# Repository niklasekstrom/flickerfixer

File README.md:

# flickerfixer
An open source flicker fixer for Amiga 500/2000

This is the first stage in the construction of a flicker fixer/scan doubler that mounts internally in an Amiga 500 or Amiga 2000.

In order to rapidly prototype the FPGA logic I designed a small adapter board that connects pins on Denise to a [DE10-Lite](http://de10-lite.terasic.com/) FPGA development board via a 5V-tolerant buffer. The KiCad files for the board are available in [Hardware](Hardware).

After ordering, receiving and soldering the PCB I then wrote Verilog code that samples CSYNC (composite sync) and the 12-bit RGB signals, and outputs the sampled pixels to VGA. The logic handles both non-interlaced and interlaced output from the Amiga. The Quartus project is available in [HDL](HDL).

The next stage is to design a stand-alone board that contains an [FPGA](https://www.mouser.se/ProductDetail/Intel-Altera/10M02SCE144C8G?qs=G%2FX6g08h60tD7HZOc4xZbg%3D%3D) chip and an [SDRAM](https://www.mouser.se/ProductDetail/ISSI/IS42S16400J-6TL?qs=sGAEpiMZZMti5BT4iPSEnRbV70NKySN8V%252BBluA5se8I%3D) chip.

Some pictures:

|         |            |
| ------------- |---------------|
|  |  |
| |  |

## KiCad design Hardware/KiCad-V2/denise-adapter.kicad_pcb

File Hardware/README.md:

# Components

* A single [74LCX16244](https://www.mouser.se/ProductDetail/ON-Semiconductor-Fairchild/74LCX16244MTD?qs=sGAEpiMZZMuiiWkaIwCK2a5G6tOfghZ%2FVIxKNPvFHco%3D) buffer chip is used to translate 5V to 3.3V.
* Four 100 nF decoupling capacitors, 1206 size, are mounted on the back of the PCB.
* A 48 pin DIP socket.
* A 48 pin DIP socket whose pins going both up and down, and the legs going down are thinner.
* A 2x20 pin ribbon cable connector.

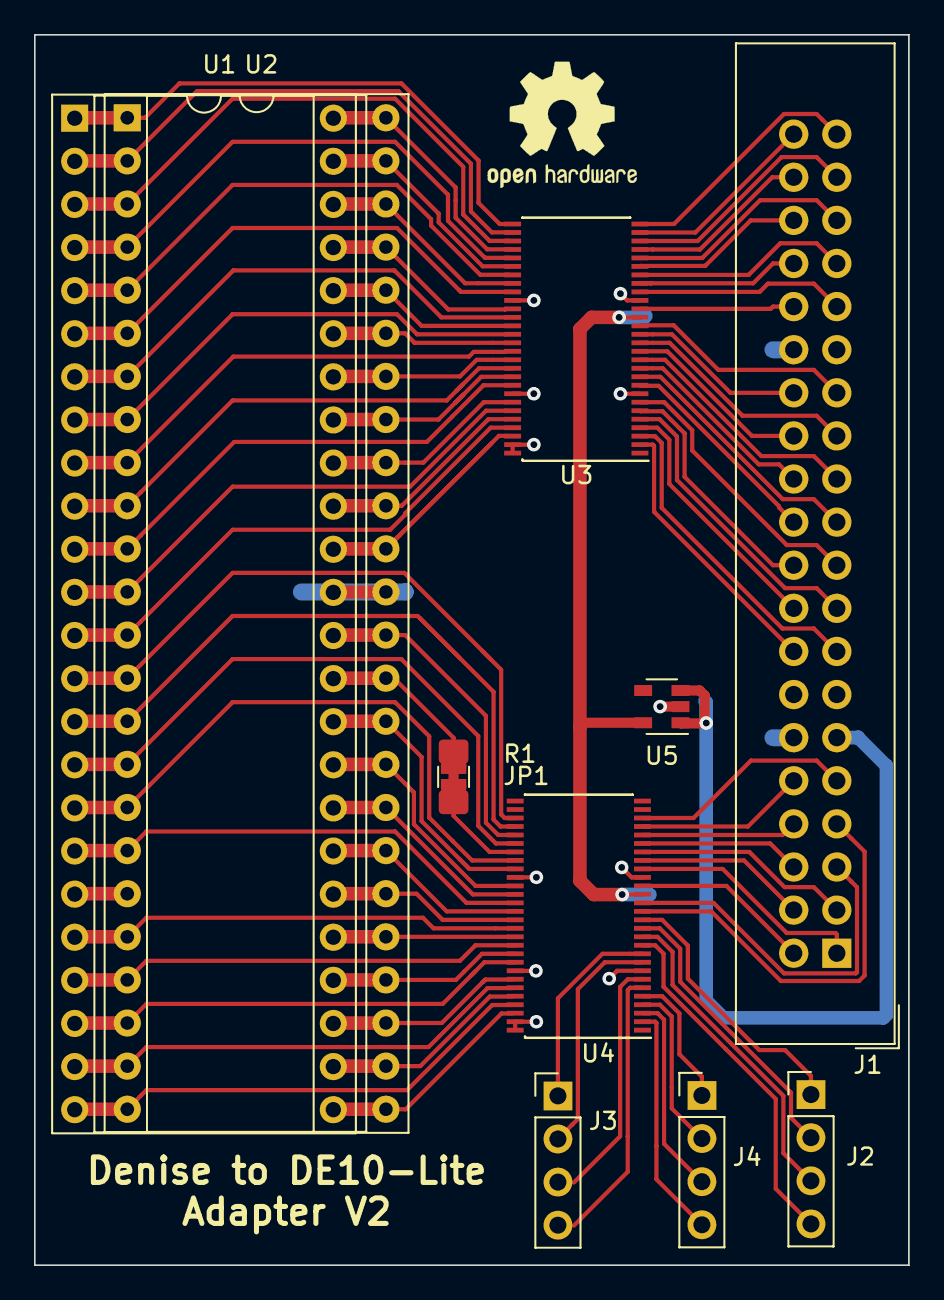
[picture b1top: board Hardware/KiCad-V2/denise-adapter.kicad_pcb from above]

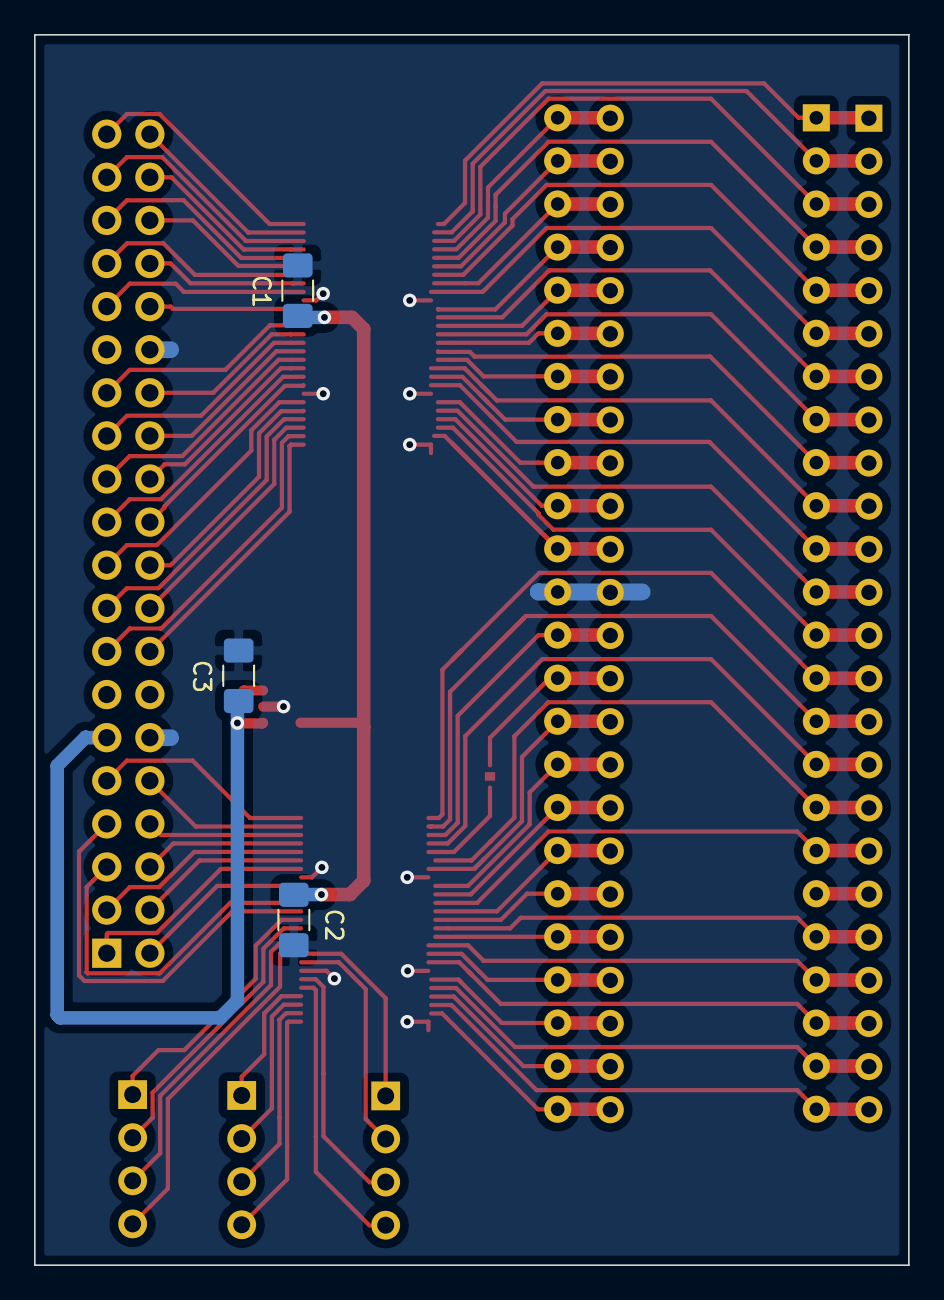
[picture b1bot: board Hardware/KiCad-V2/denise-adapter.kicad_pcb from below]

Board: 2 copper layers, 51.5 x 72.5 mm, 14 parts (3 on the bottom side), 97 nets.

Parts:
C1, C2, C3: 100n; C_1206_3216Metric_Pad1.42x1.75mm_HandSolder
J1: Conn_02x20_Odd_Even; IDC-Header_2x20_P2.54mm_Vertical
J2, J3, J4: Conn_01x04; PinHeader_1x04_P2.54mm_Vertical
JP1: SolderJumper_2_Bridged; SolderJumper-2_P1.3mm_Bridged_RoundedPad1.0x1.5mm
R1: 33; R_1206_3216Metric_Pad1.42x1.75mm_HandSolder
U1: Denise; DIP-48_W15.24mm_Socket_0.9dia
U2: Denise; DIP-48_W15.24mm_Socket
U3, U4: SN74CBT16211A; TSSOP-56_6.1x14mm_P0.5mm
U5: TPS73643DBV; SOT-23-5

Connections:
3VB0: J4.3, U4.3
3VB1: J4.4, U4.2
3VB2: J4.2, U4.4
3VB3: J3.4, U4.6
3VBURST: J1.7, U4.15
3VC7M: J1.3, U4.22
3VCCK: J1.8, U4.24
3VCDAC: J1.1, U4.20
3VCSYNC: J1.5, U4.16
3VD0: J1.27, U3.16
3VD1: J1.31, U3.20
3VD2: J1.33, U3.22
3VD3: J1.35, U3.24
3VD4: J1.37, U3.26
3VD5: J1.40, U3.27
3VD6: J1.39, U3.28
3VD7: J1.38, U3.25
3VD8: J1.36, U3.23
3VD9: J1.34, U3.21
3VD10: J1.32, U3.18
3VD11: J1.28, U3.15
3VD12: J1.26, U3.13
3VD13: J1.24, U3.11
3VD14: J1.22, U3.9
3VD15: J1.20, U3.6
3VG0: J3.2, U4.9
3VG1: J2.4, U4.11
3VG2: J2.2, U4.13
3VG3: J2.1, U4.14
3VM0H: J1.23, U3.12
3VM0V: J1.16, U3.2
3VM1H: J1.25, U3.14
3VM1V: J1.18, U3.4
3VR0: J2.3, U4.12
3VR1: J3.1, U4.10
3VR2: J3.3, U4.7
3VR3: J4.1, U4.5
3VRGA1: J1.4, U4.21
3VRGA2: J1.6, U4.23
3VRGA3: J1.10, U4.25
3VRGA4: J1.9, U4.26
3VRGA5: J1.15, U3.3
3VRGA6: J1.17, U3.5
3VRGA7: J1.19, U3.7
3VRGA8: J1.21, U3.10
3VZD: J1.2, U4.18
+4V3: C1.1, C2.1, U3.17, U4.17, U5.5
+5V: C3.1, J1.11, U5.1, U5.3
AM_VCC: U1.19, U2.19
B0: U1.24, U2.24, U4.53
B1: U1.25, U2.25, U4.54
B2: U1.26, U2.26, U4.52
B3: U1.27, U2.27, U4.50
BURST: U1.18, U2.18, U4.41
C7M: JP1.1, R1.2, U1.35, U2.35
CCK: U1.36, U2.36, U4.33
CDAC: U1.34, U2.34, U4.37
CSYNC: U1.32, U2.32, U4.40
D0: U1.7, U2.7, U3.40
D1: U1.6, U2.6, U3.37
D2: U1.5, U2.5, U3.35
D3: U1.4, U2.4, U3.33
D4: U1.3, U2.3, U3.31
D5: U1.2, U2.2, U3.30
D6: U1.1, U2.1, U3.29
D7: U1.48, U2.48, U3.32
D8: U1.47, U2.47, U3.34
D9: U1.46, U2.46, U3.36
D10: U1.45, U2.45, U3.39
D11: U1.44, U2.44, U3.41
D12: U1.43, U2.43, U3.43
D13: U1.42, U2.42, U3.45
D14: U1.41, U2.41, U3.47
D15: U1.40, U2.40, U3.50
G0: U1.28, U2.28, U4.47
G1: U1.29, U2.29, U4.45
G2: U1.30, U2.30, U4.43
G3: U1.31, U2.31, U4.42
GND: C1.2, C2.2, C3.2, J1.12, J1.30, U1.37, U2.37, U3.8, U3.19, U3.38, U3.49, U3.55, U3.56, U4.8, U4.19, U4.38, U4.49, U4.55, U4.56, U5.2
M0H: U1.9, U2.9, U3.44
M0V: U1.38, U2.38, U3.54
M1H: U1.8, U2.8, U3.42
M1V: U1.39, U2.39, U3.52
unnamed: JP1.2, R1.1, U4.35
R0: U1.20, U2.20, U4.44
R1: U1.21, U2.21, U4.46
R2: U1.22, U2.22, U4.48
R3: U1.23, U2.23, U4.51
RGA1: U1.17, U2.17, U4.36
RGA2: U1.16, U2.16, U4.34
RGA3: U1.15, U2.15, U4.32
RGA4: U1.14, U2.14, U4.31
RGA5: U1.13, U2.13, U3.53
RGA6: U1.12, U2.12, U3.51
RGA7: U1.11, U2.11, U3.48
RGA8: U1.10, U2.10, U3.46
ZD: U1.33, U2.33, U4.39

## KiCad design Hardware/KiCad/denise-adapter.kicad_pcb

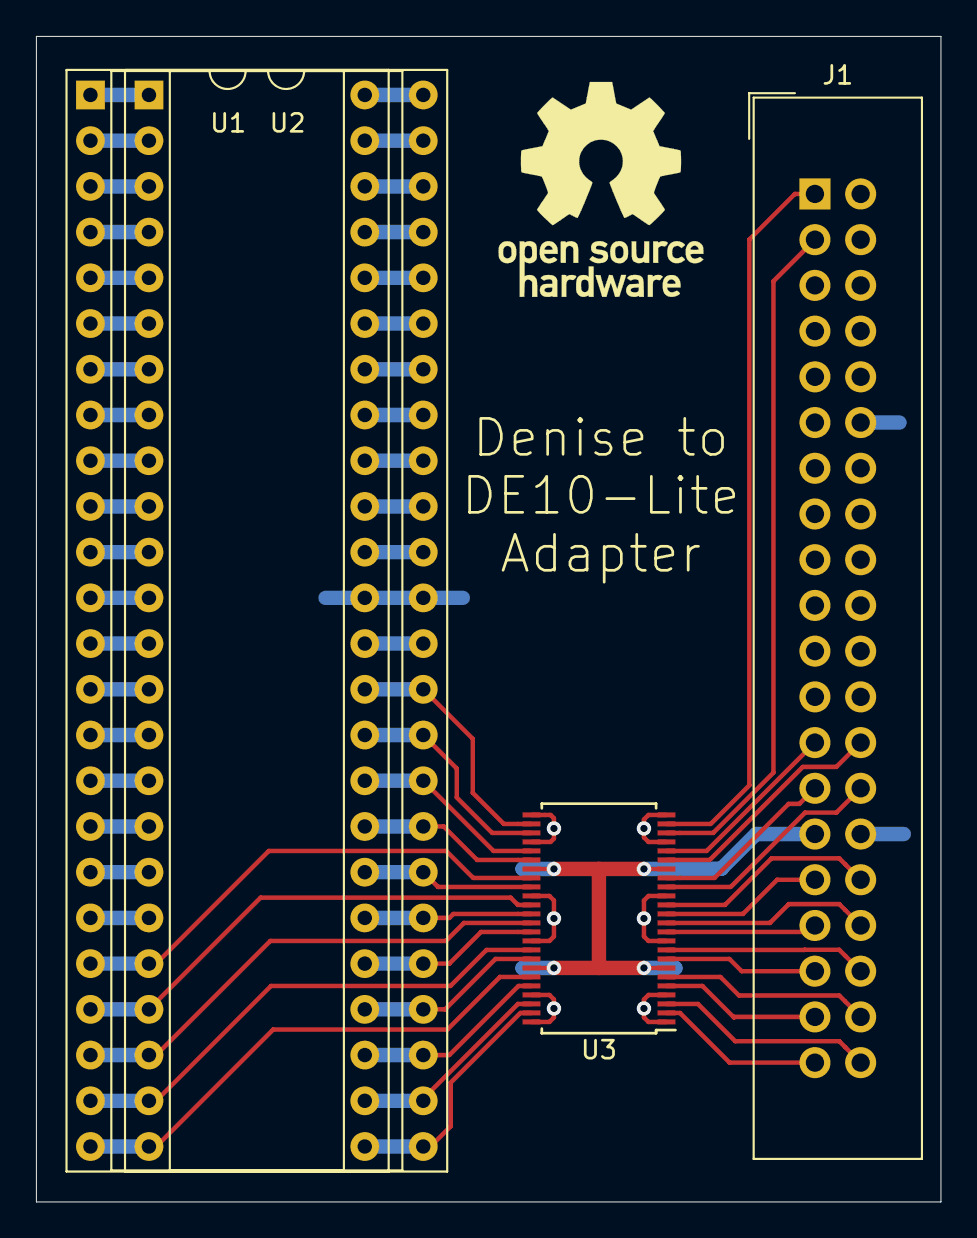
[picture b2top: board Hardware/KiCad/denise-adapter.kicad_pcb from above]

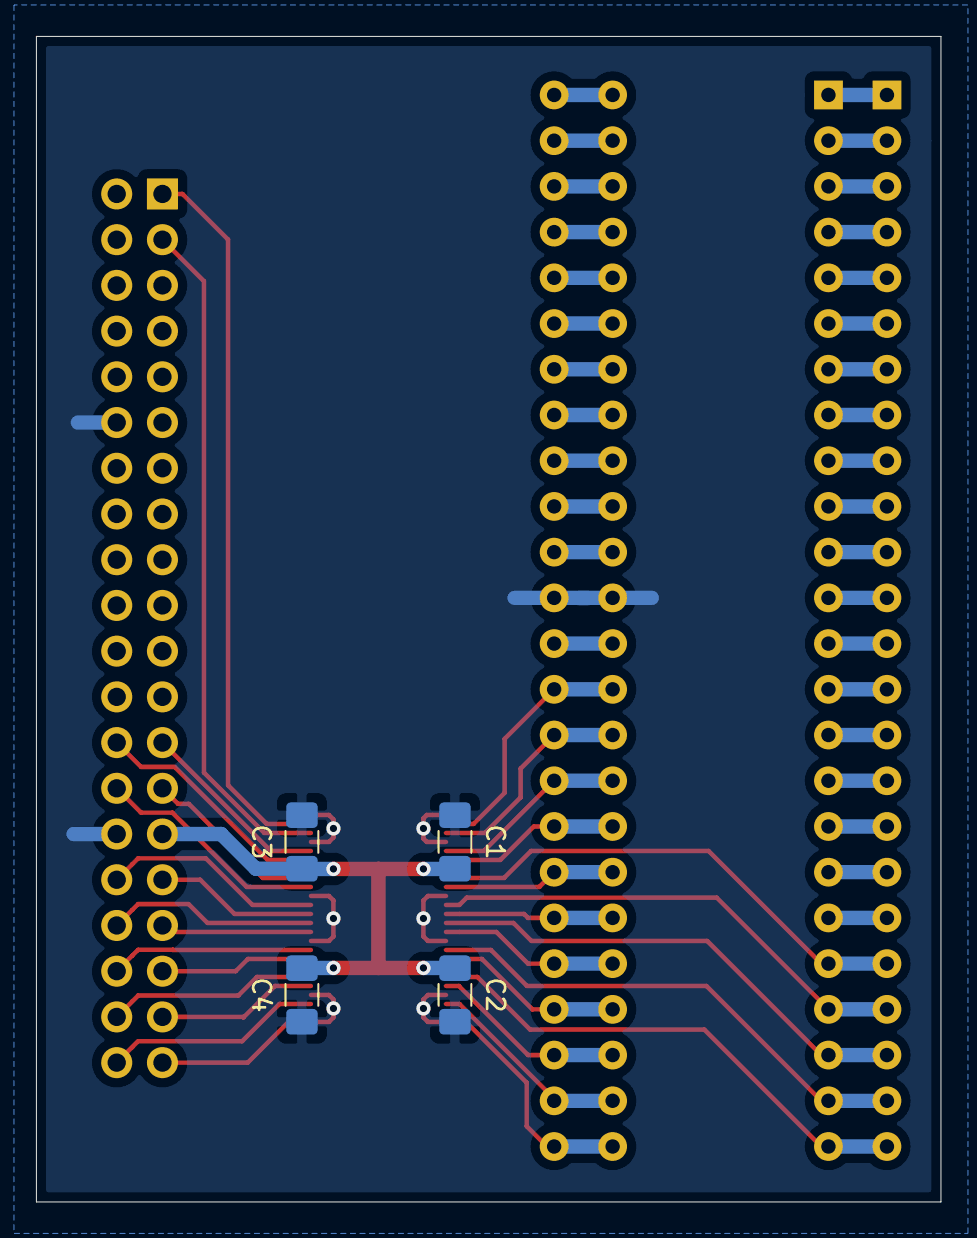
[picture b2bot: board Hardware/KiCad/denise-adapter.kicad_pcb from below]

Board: 2 copper layers, 50.2 x 64.8 mm, 8 parts (4 on the bottom side), 65 nets.

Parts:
C1, C2, C3, C4: 100n; C_1206_3216Metric_Pad1.42x1.75mm_HandSolder
J1: Conn_02x20_Odd_Even; IDC-Header_2x20_P2.54mm_Vertical
U1, U2: 8373_DeniseECS-AmigaCustomChips; DIP-48_W15.24mm_Socket
U3: SN74LVC16244ADGGR; TSSOP-48_6.1x12.5mm_P0.5mm

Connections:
3V7M: J1.1, U3.23
3VB0: J1.38, U3.6
3VB1: J1.39, U3.2
3VB2: J1.40, U3.3
3VB3: J1.37, U3.5
3VCDAC: J1.3, U3.22
3VCSYNC: J1.26, U3.19
3VG0: J1.35, U3.8
3VG1: J1.33, U3.11
3VG2: J1.31, U3.13
3VG3: J1.28, U3.16
3VPIXELSW: J1.25, U3.20
3VR0: J1.27, U3.17
3VR1: J1.32, U3.14
3VR2: J1.34, U3.12
3VR3: J1.36, U3.9
7M: U1.35, U2.35, U3.26
+3V3: C1.1, C2.1, C3.1, C4.1, J1.29, U3.7, U3.18, U3.31, U3.42
+5V: U1.19, U2.19
B0: U1.24, U2.24, U3.43
B1: U1.25, U2.25, U3.47
B2: U1.26, U2.26, U3.46
B3: U1.27, U2.27, U3.44
BURST: U1.18, U2.18
CCK: U1.36, U2.36
CDAC: U1.34, U2.34, U3.27
CSYNC: U1.32, U2.32, U3.30
DRD0: U1.7, U2.7
DRD1: U1.6, U2.6
DRD2: U1.5, U2.5
DRD3: U1.4, U2.4
DRD4: U1.3, U2.3
DRD5: U1.2, U2.2
DRD6: U1.1, U2.1
DRD7: U1.48, U2.48
DRD8: U1.47, U2.47
DRD9: U1.46, U2.46
DRD10: U1.45, U2.45
DRD11: U1.44, U2.44
DRD12: U1.43, U2.43
DRD13: U1.42, U2.42
DRD14: U1.41, U2.41
DRD15: U1.40, U2.40
G0: U1.28, U2.28, U3.41
G1: U1.29, U2.29, U3.38
G2: U1.30, U2.30, U3.36
G3: U1.31, U2.31, U3.33
GND: C1.2, C2.2, C3.2, C4.2, J1.12, J1.30, U1.37, U2.37, U3.1, U3.4, U3.10, U3.15, U3.21, U3.24, U3.25, U3.28, U3.34, U3.39, U3.45, U3.48
M0H: U1.9, U2.9
M0V: U1.38, U2.38
M1H: U1.8, U2.8
M1V: U1.39, U2.39
PIXELSW: U1.33, U2.33, U3.29
R0: U1.20, U2.20, U3.32
R1: U1.21, U2.21, U3.35
R2: U1.22, U2.22, U3.37
R3: U1.23, U2.23, U3.40
RGA1: U1.17, U2.17
RGA2: U1.16, U2.16
RGA3: U1.15, U2.15
RGA4: U1.14, U2.14
RGA5: U1.13, U2.13
RGA6: U1.12, U2.12
RGA7: U1.11, U2.11
RGA8: U1.10, U2.10

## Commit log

2020-01-10 Added hardware and HDL designs
    The HDL contains two subdirectories, 1280x800 and 1280x1024, that correspond to
    designs that output to those two VGA resolutions. The differences between the
    files in the subdirectories are few and small, and if I figure out a way it
    would be nicer to combine them into one project, presumably using some sort of
    preprocessor directives.
2020-01-10 Update components list
2020-03-18 Added KiCad files for Denise adapter v2
2020-03-18 Should use SN74CBT16211A, not SN74CBTD16211
2020-03-18 Fixed label +4V to correct value +4V3
